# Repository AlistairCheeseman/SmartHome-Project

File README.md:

SmartHome-Project
=================

Final Year degree project to create a set of devices to create a smart home.

Hardware files are created in eagle with PDFs of finished pcbs labelled with which pcb layer they are. Hardware files are created from scratch and a custom library has been created for components not in the default eagle library.

Software has three sections.

	-	www
		copy this to the production web server. the files are based on php 5.6 HTML 5, using ajax and highcharts charting components (http://www.highcharts.com/ - free for non commercial uses).
		
	-	LFS
		This contains a set of manually written build scripts (toolchain and Filesystem) and pre-writted configuration files. After both files (install-*.sh) have been executed on a linux machine there will be a working Linux filesystem. Be sure to change configuration file (buildscript.sh) variables to suit your setup!

	-	Apps
		This contains source for all custom written applications on the server.

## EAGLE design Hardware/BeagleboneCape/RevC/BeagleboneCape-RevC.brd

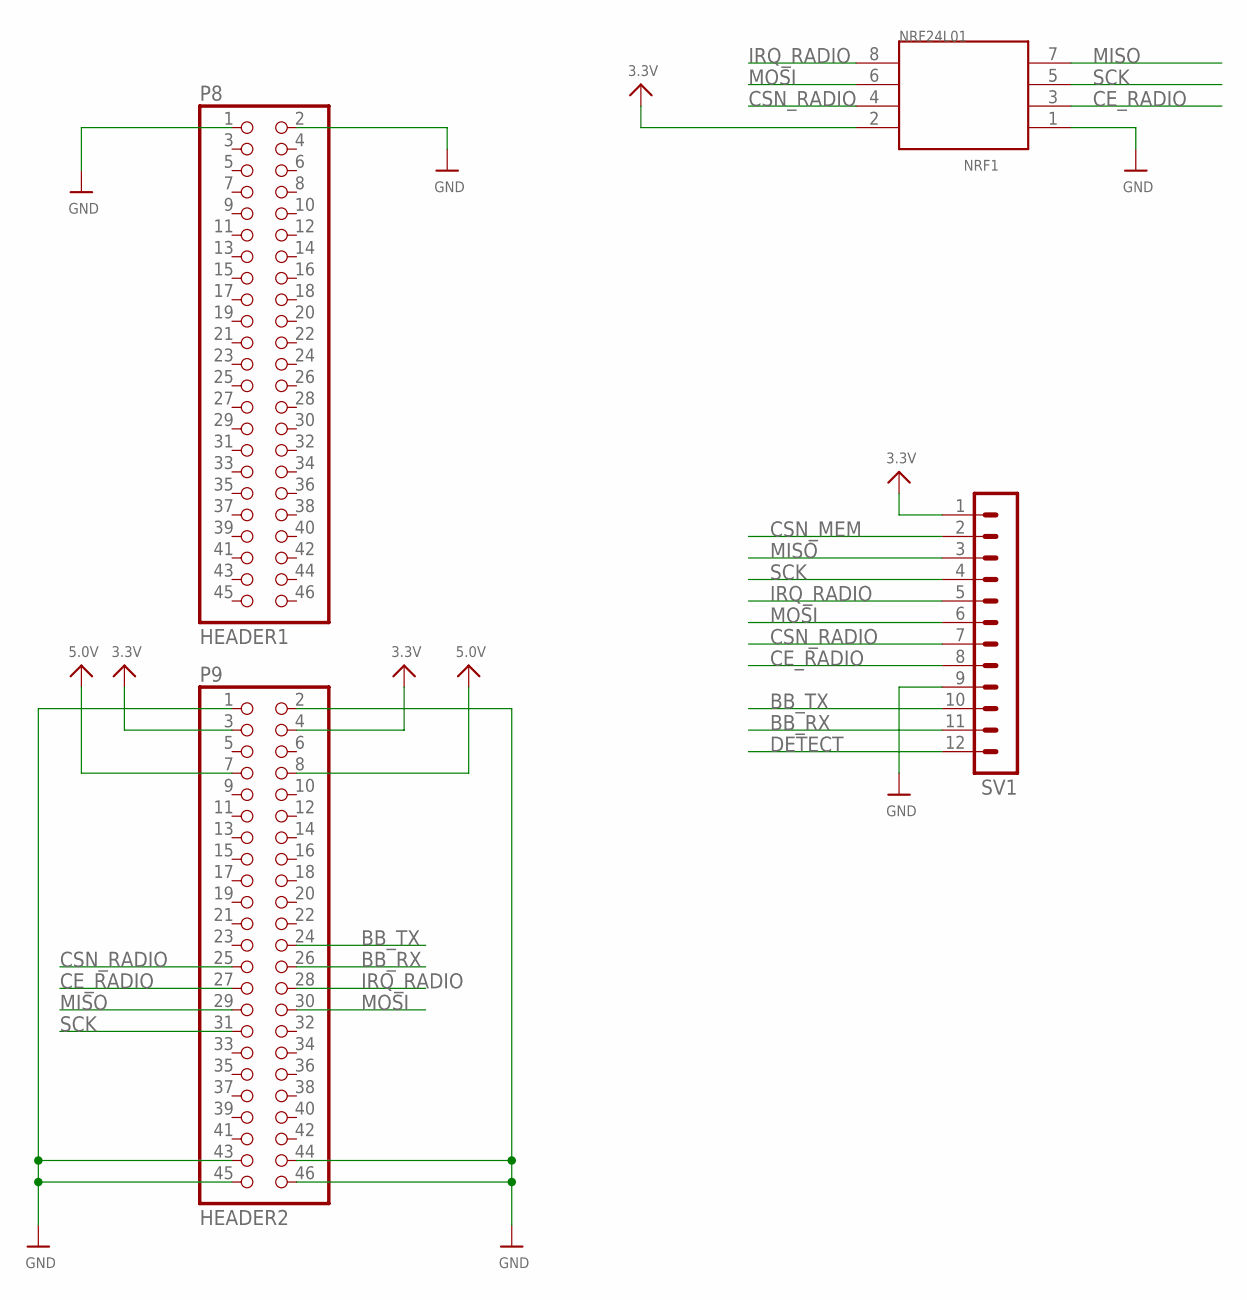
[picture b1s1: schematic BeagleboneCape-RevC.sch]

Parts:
NRF24L01: NRF1; TSM-110-XX-XXX-DV
P8: HEADER1; 2X23
P9: HEADER2; 2X23
SV1: MA12-1

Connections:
3.3V: NRF24L01.2, P9.3, P9.4, SV1.1
5.0V: P9.7, P9.8
BB_RX: P9.26, SV1.11
BB_TX: P9.24, SV1.10
CE_RADIO: NRF24L01.3, P9.27, SV1.8
CSN_MEM: SV1.2
CSN_RADIO: NRF24L01.4, P9.25, SV1.7
DETECT: SV1.12
GND: NRF24L01.1, P8.1, P8.2, P9.1, P9.2, P9.43, P9.44, P9.45, P9.46, SV1.9
IRQ_RADIO: NRF24L01.8, P9.28, SV1.5
MISO: NRF24L01.7, P9.29, SV1.3
MOSI: NRF24L01.6, P9.30, SV1.6
SCK: NRF24L01.5, P9.31, SV1.4

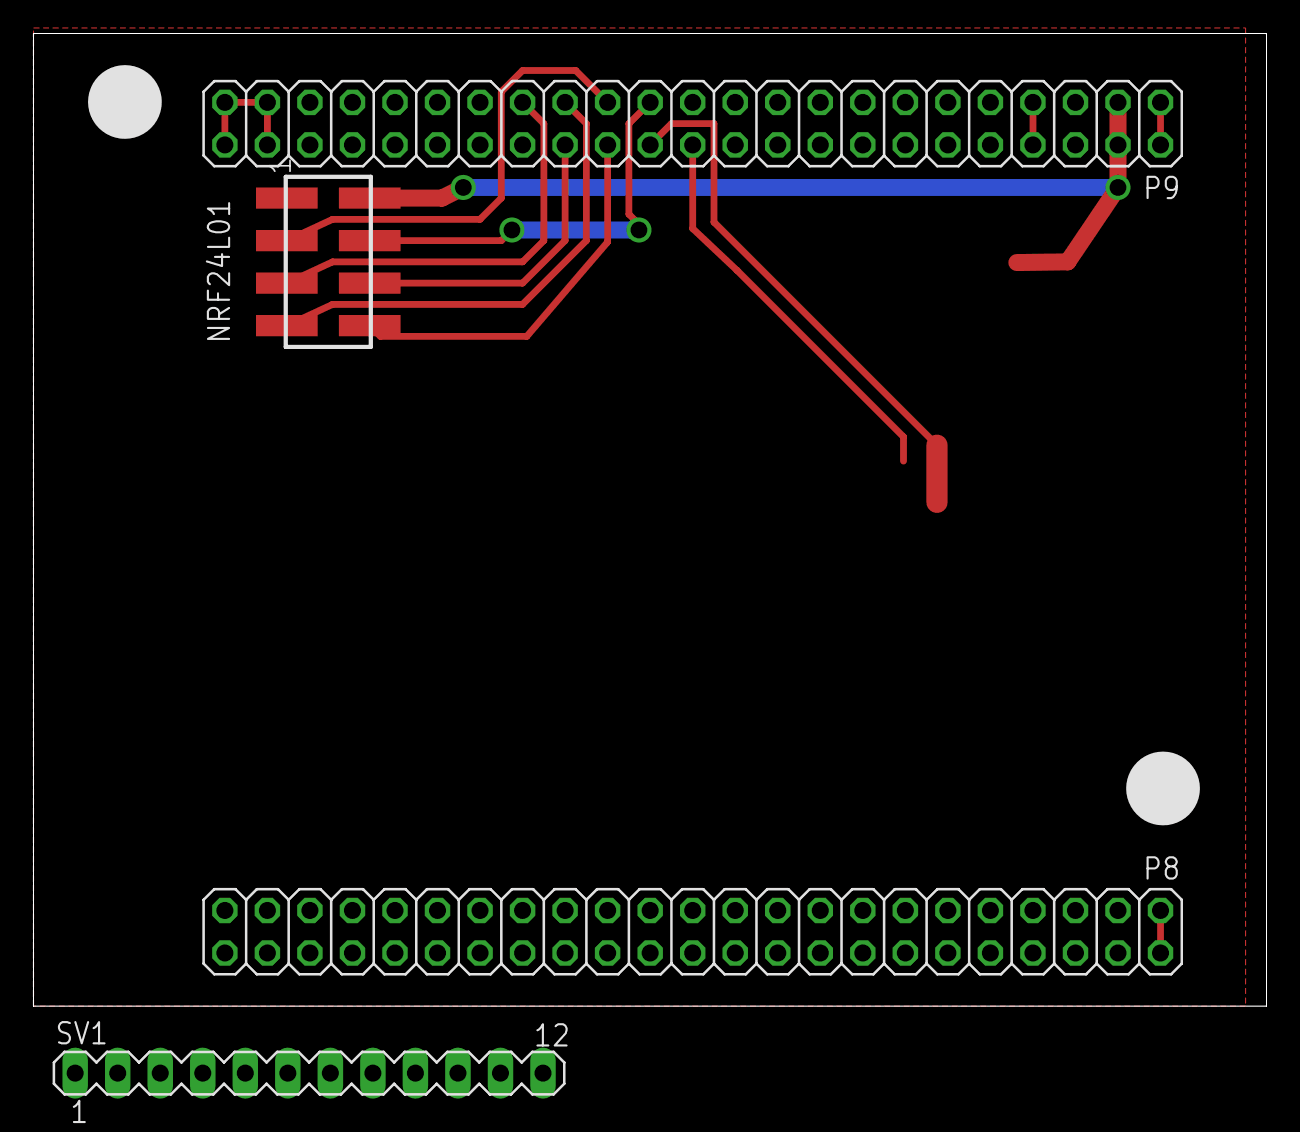
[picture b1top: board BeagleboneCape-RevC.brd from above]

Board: 2 copper layers, 73.6 x 58.1 mm, 4 parts (0 on the bottom side), 11 nets.

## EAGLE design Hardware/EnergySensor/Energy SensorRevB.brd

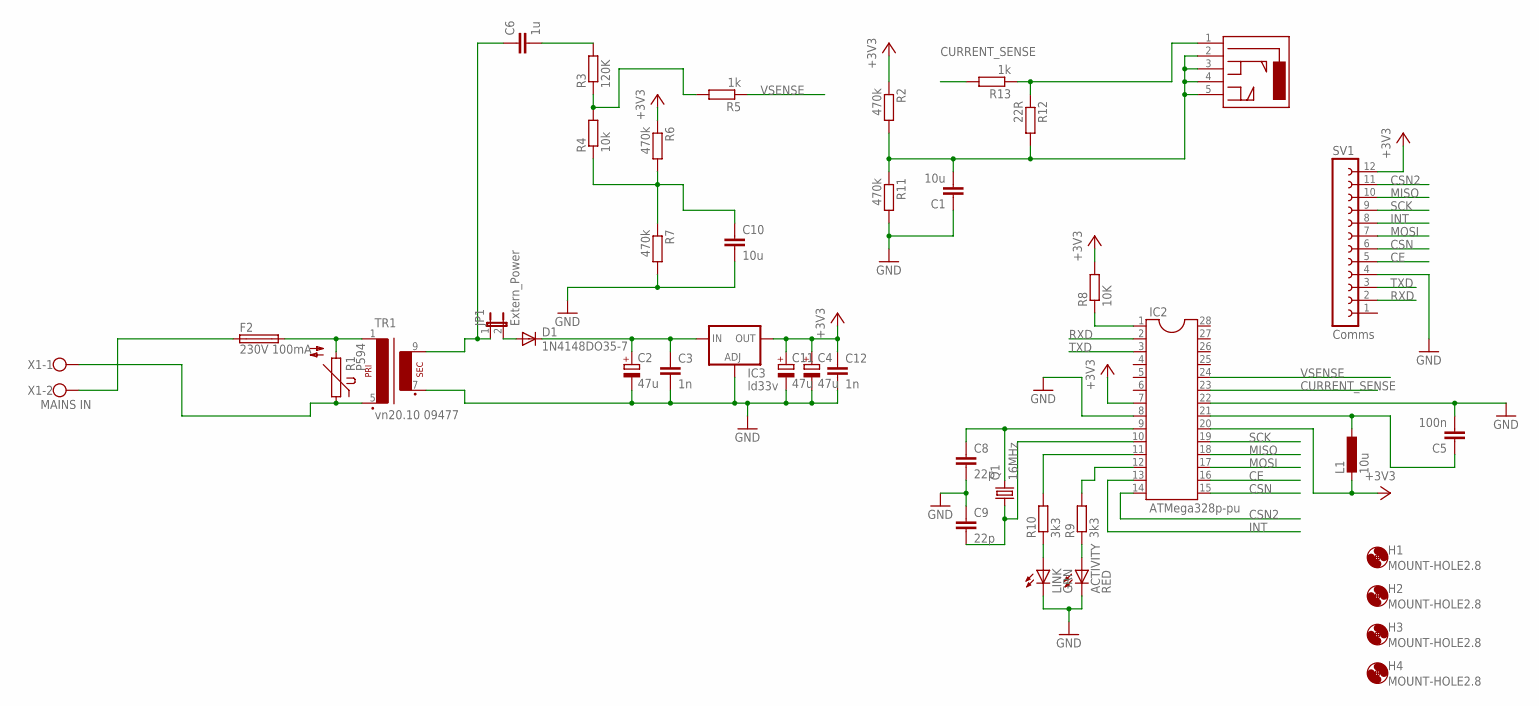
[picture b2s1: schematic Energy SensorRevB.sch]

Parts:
ACTIVITY: RED; LED5MM
C1, C10: 10u; C1206K
C2: 47u; E3,5-10
C3, C12: 1n; C025-025X050
C4, C11: 47u; E3,5-8
C5: 100n; C1206K
C6: 1u; C1206K
C8, C9: 22p; C025-025X050
D1: 1N4148DO35-7; DO35-7
F2: 230V 100mA; SH22,5A
H1, H2, H3, H4: MOUNT-HOLE2.8; 2,8
IC2: ATMega328p-pu; DIL28-3
IC3: ld33v; 317TL
JP1: Extern_Power; JP1
L1: 10u; L3230M
LINK: GRN; LED5MM
Q1: 16MHz; HC49/S
R1: P594
R2, R6, R7, R11: 470k; 0207/7
R3: 120K; 0207/7
R4: 10k; R1206
R5, R13: 1k; 0207/7
R8: 10K; 0207/7
R9, R10: 3k3; 0207/7
R12: 22R; R1206
SV1: Comms; FE12W
TR1: vn20.10 09477; VV11
U$1: 3.5MMJACK
X1: MAINS IN; W237-102

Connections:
+3V3: C4.+, C11.+, C12.1, IC2.7, IC2.20, IC3.2 (OUT), L1.2, R2.1, R6.1, R8.2, SV1.12
CE: IC2.16, SV1.5
CSN: IC2.15, SV1.6
CSN2: IC2.14, SV1.11
CURRENT_SENSE: IC2.23, R13.2
GND: ACTIVITY.K (C), C1.1, C2.-, C3.2, C4.-, C5.2, C8.2, C9.1, C10.2, C11.-, C12.2, IC2.8, IC2.22, IC3.1 (ADJ), LINK.K (C), R7.2, R11.2, SV1.4, TR1.7 (S3)
INT: IC2.13, SV1.8
MISO: IC2.18, SV1.10
MOSI: IC2.17, SV1.7
unnamed: C1.2, R2.2, R11.1, R12.2, U$1.2, U$1.3, U$1.4, U$1.5
unnamed: R1.1, TR1.5 (P2), X1.1
unnamed: D1.A, JP1.2
unnamed: C6.2, R3.2
unnamed: C6.1, JP1.1, TR1.9 (S4)
unnamed: R12.1, R13.1, U$1.1
unnamed: C2.+, C3.1, D1.C, IC3.3 (IN)
unnamed: C5.1, IC2.21, L1.1
unnamed: R3.1, R4.2, R5.2
unnamed: C10.1, R4.1, R6.2, R7.1
unnamed: C8.1, IC2.9, Q1.2
unnamed: C9.2, IC2.10, Q1.1
unnamed: LINK.A, R10.1
unnamed: ACTIVITY.A, R9.1
unnamed: IC2.1, R8.1
unnamed: IC2.12, R9.2
unnamed: IC2.11, R10.2
unnamed: F2.2, R1.2, TR1.1
unnamed: F2.1, X1.2
RXD: IC2.2, SV1.2
SCK: IC2.19, SV1.9
TXD: IC2.3, SV1.3
VSENSE: IC2.24, R5.1

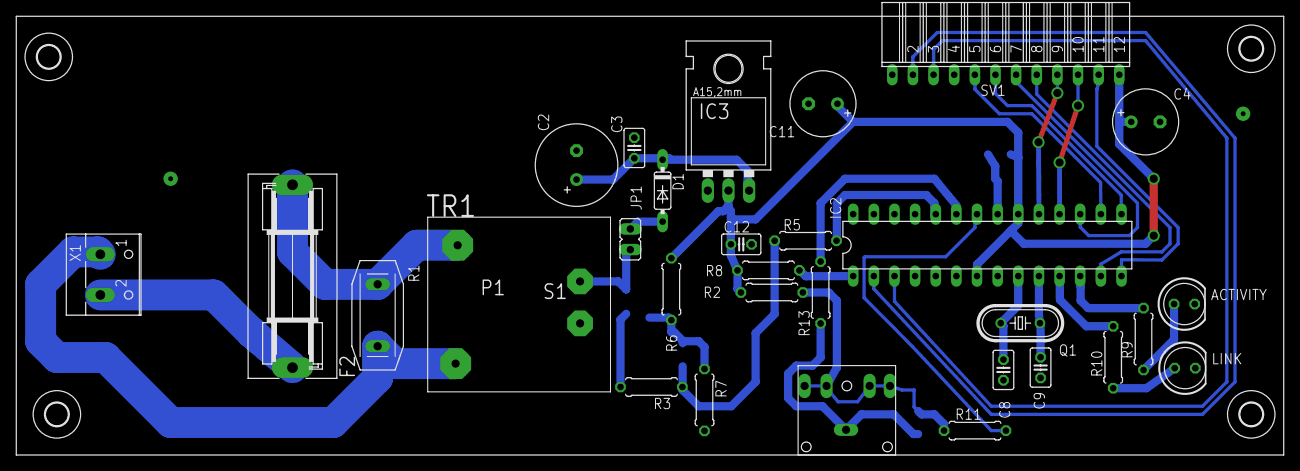
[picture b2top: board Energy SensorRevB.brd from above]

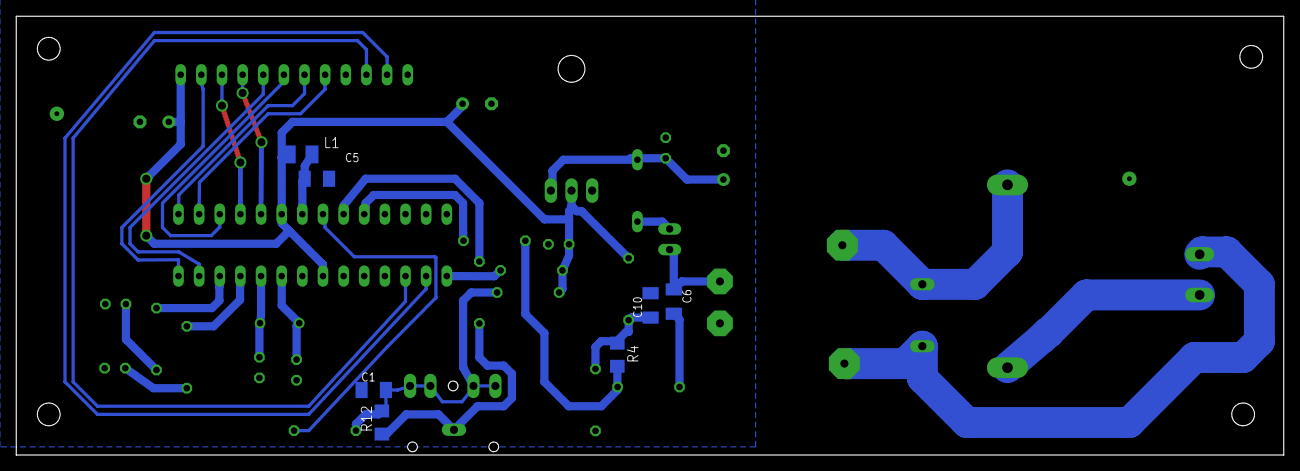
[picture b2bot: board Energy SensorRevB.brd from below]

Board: 2 copper layers, 156.0 x 54.0 mm, 41 parts (7 on the bottom side), 32 nets.

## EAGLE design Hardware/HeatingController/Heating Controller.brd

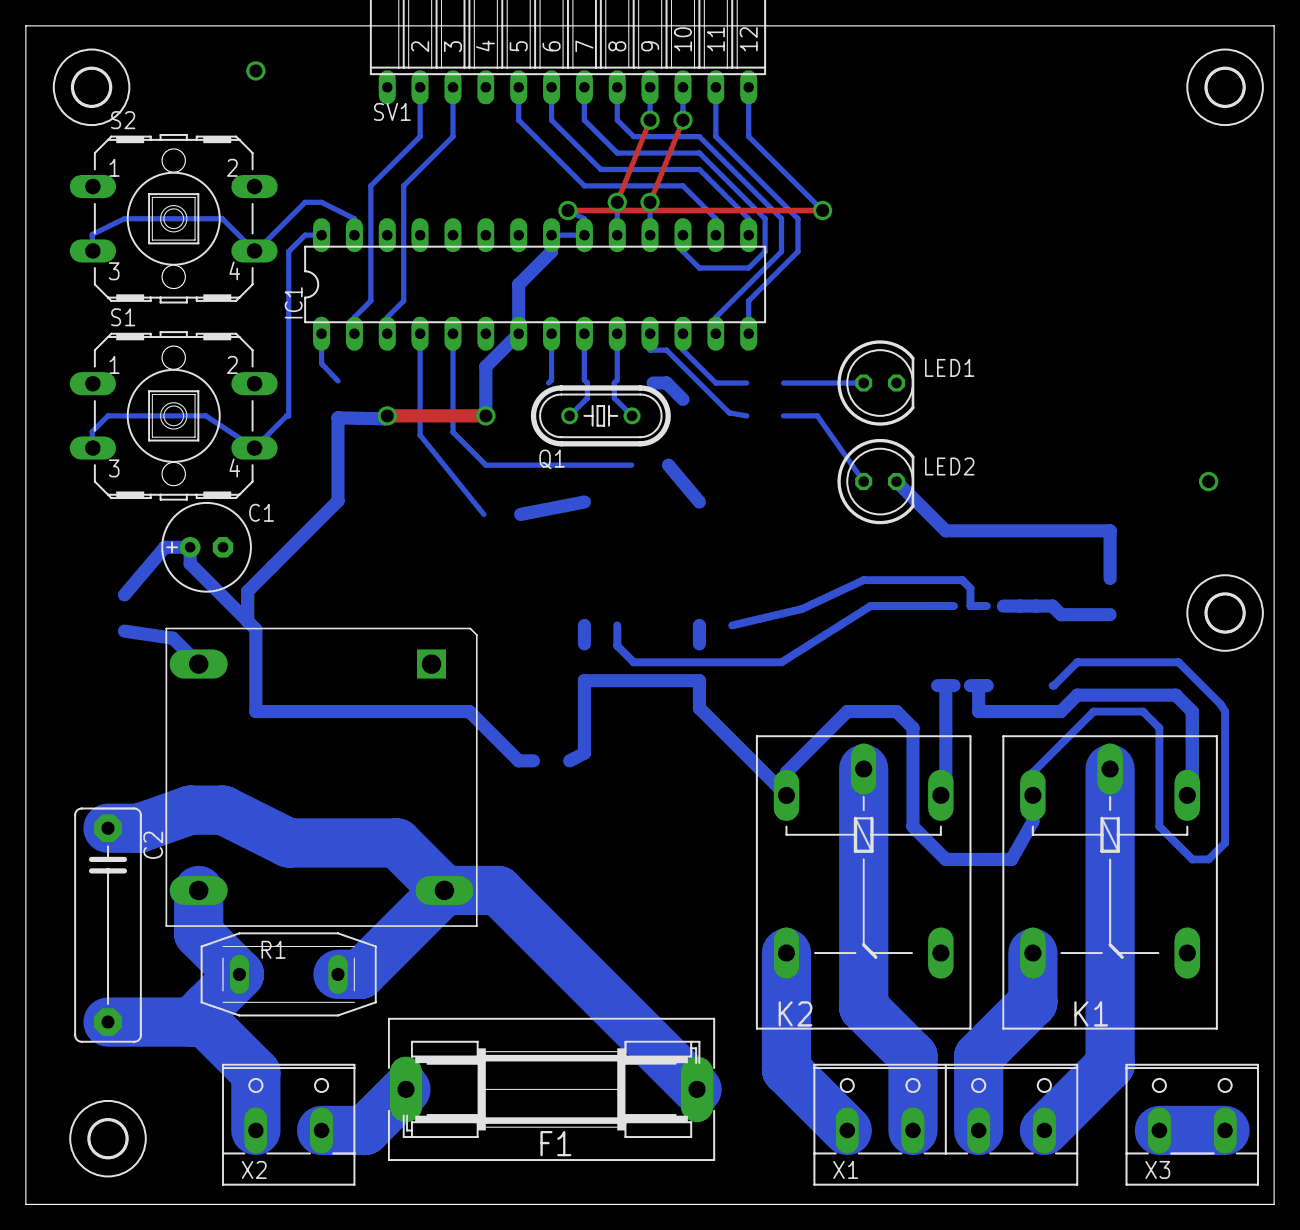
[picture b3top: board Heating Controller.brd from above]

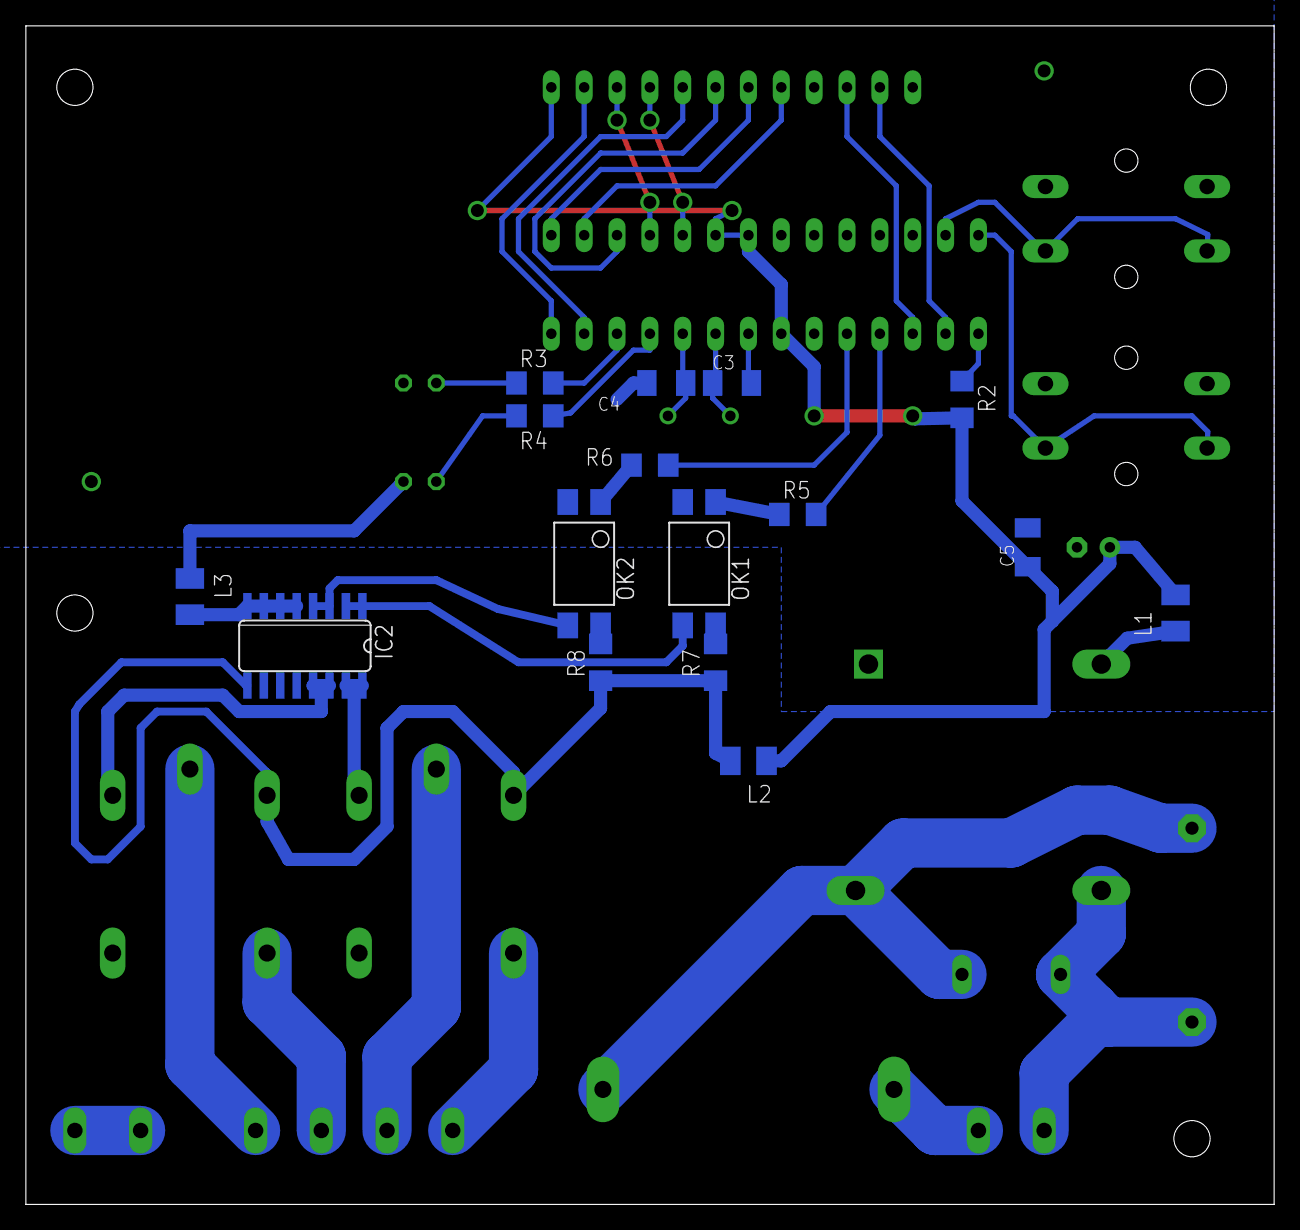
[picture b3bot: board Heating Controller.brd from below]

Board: 2 copper layers, 96.5 x 91.1 mm, 37 parts (16 on the bottom side), 41 nets.

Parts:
C1: 47u; E2,5-7
C2: 0.1u/275V; C15B5
C3, C4: 22p; C1206K
C5: 0.1u; C1206K
F1: 230V 70mA; SH22,5A
H1, H2, H3, H4: MOUNT-HOLE2.8; 2,8
IC1: ATMega 328p-pu; DIL28-3
IC2: ULN2003AD; SO16
K1, K2: G5LE
L1, L2, L3: L3230M
LED1: HEAT; LED5MM
LED2: WATER; LED5MM
OK1, OK2: LTV816S; DIL4-SMD
Q1: 16MHz; HC49/S
R1: P594
R2: 10k; R1206
R3, R4: 3k3; R1206
R5, R6, R7, R8: 120R; R1206
S1: WATER_BOOST; B3F-40XX
S2: HEATING_BOOST; B3F-40XX
SV1: Comms; FE12W
U$1: VTX-214-001-103; VTX214001103
X1: SWITCHED_OUT; W237-4P
X2: MAINS IN; W237-132
X3: NEUTRAL; W237-132

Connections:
+3V3: C1.+, C5.1, IC1.7, IC1.20, IC1.21, L1.2, L2.1, R2.2, SV1.12
+3V3A: L1.1, U$1.2
AGND: IC2.5, IC2.6, IC2.7, IC2.8, L3.2
CE: IC1.16, SV1.5
CSN: IC1.15, SV1.6
CSN2: IC1.14, SV1.11
GND: C1.-, C3.2, C4.2, C5.2, IC1.8, IC1.22, L3.1, LED1.K, LED2.K, OK1.2, OK2.2, S1.1, S1.2, S2.1, S2.2, SV1.4, U$1.1
HEATING_R: IC1.5, R6.2
HEATL: IC1.11, R4.2
HOTWATERL: IC1.12, R3.2
HOTWATER_R: IC1.4, R5.2
INT: IC1.13, SV1.8
MISO: IC1.18, SV1.10
MOSI: IC1.17, SV1.7
unnamed: F1.1, X2.2
unnamed: C2.1, F1.2, R1.2, U$1.4
unnamed: C2.2, R1.1, U$1.3, X2.1
unnamed: IC1.1, R2.1
unnamed: C3.1, IC1.9, Q1.2
unnamed: C4.1, IC1.10, Q1.1
unnamed: LED1.A, R3.1
unnamed: LED2.A, R4.1
unnamed: IC1.28, S1.3, S1.4
unnamed: IC1.27, S2.3, S2.4
unnamed: OK1.1, R5.1
unnamed: IC2.15, IC2.16, K2.2
unnamed: IC2.13, IC2.14, K1.2
unnamed: OK2.1, R6.1
unnamed: K2.P, X1.2
unnamed: K2.S, X1.1
unnamed: K1.P, X1.4
unnamed: K1.S, X1.3
unnamed: X3.1, X3.2
unnamed: OK1.4, R7.2
unnamed: OK2.4, R8.2
unnamed: IC2.1, IC2.2, OK1.3
unnamed: IC2.3, IC2.4, OK2.3
RXD: IC1.2, SV1.2
SCK: IC1.19, SV1.9
TXD: IC1.3, SV1.3
VCC: IC2.9, K1.1, K2.1, L2.2, R7.1, R8.1

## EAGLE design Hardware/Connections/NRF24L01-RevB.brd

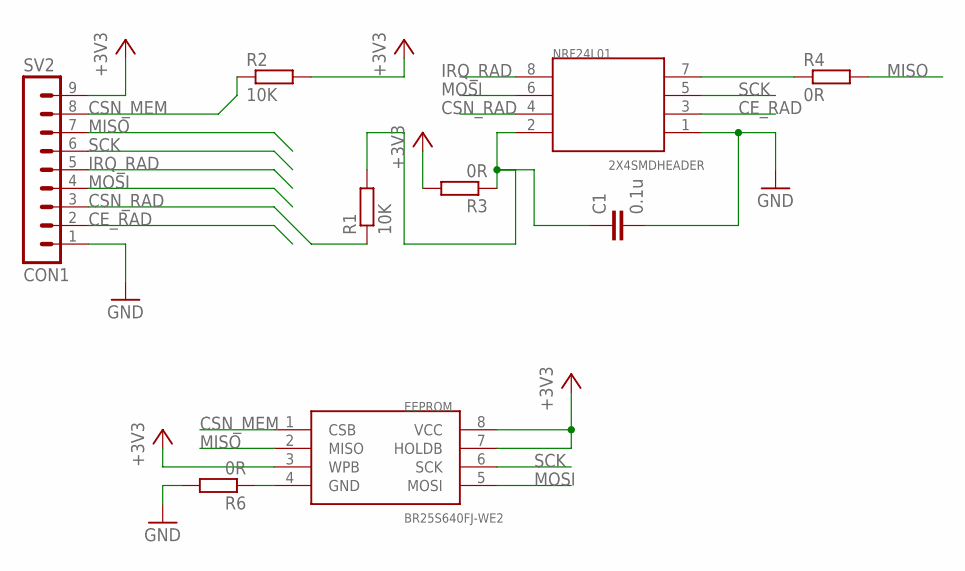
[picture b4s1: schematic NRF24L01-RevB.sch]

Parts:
C1: 0.1u; C1206K
EEPROM: BR25S640FJ-WE2; SO8
NRF24L01: 2X4SMDHEADER; TSM-110-XX-XXX-DV
R1, R2: 10K; R1206
R3, R4, R6: 0R; R1206
SV2: CON1; MA09-1W

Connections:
+3V3: EEPROM.3 (WPB), EEPROM.7 (HOLDB), EEPROM.8 (VCC), R2.2, R3.2, SV2.9
CE_RAD: NRF24L01.3, SV2.2
CSN_MEM: EEPROM.1 (CSB), R2.1, SV2.8
CSN_RAD: NRF24L01.4, R1.1, SV2.3
GND: C1.2, NRF24L01.1, R6.2, SV2.1
IRQ_RAD: NRF24L01.8, SV2.5
MISO: EEPROM.2 (MISO), R4.2, SV2.7
MOSI: EEPROM.5 (MOSI), NRF24L01.6, SV2.4
unnamed: C1.1, NRF24L01.2, R1.2, R3.1
unnamed: NRF24L01.7, R4.1
unnamed: EEPROM.4 (GND), R6.1
SCK: EEPROM.6 (SCK), NRF24L01.5, SV2.6

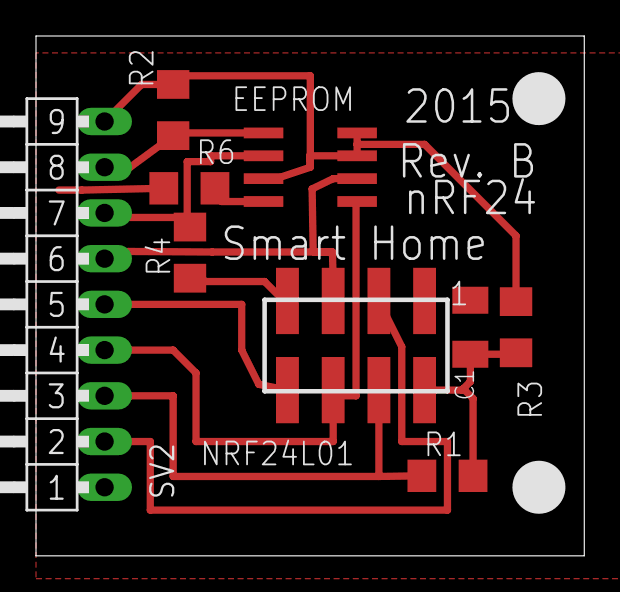
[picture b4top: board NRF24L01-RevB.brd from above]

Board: 2 copper layers, 30.5 x 28.9 mm, 9 parts (0 on the bottom side), 12 nets.

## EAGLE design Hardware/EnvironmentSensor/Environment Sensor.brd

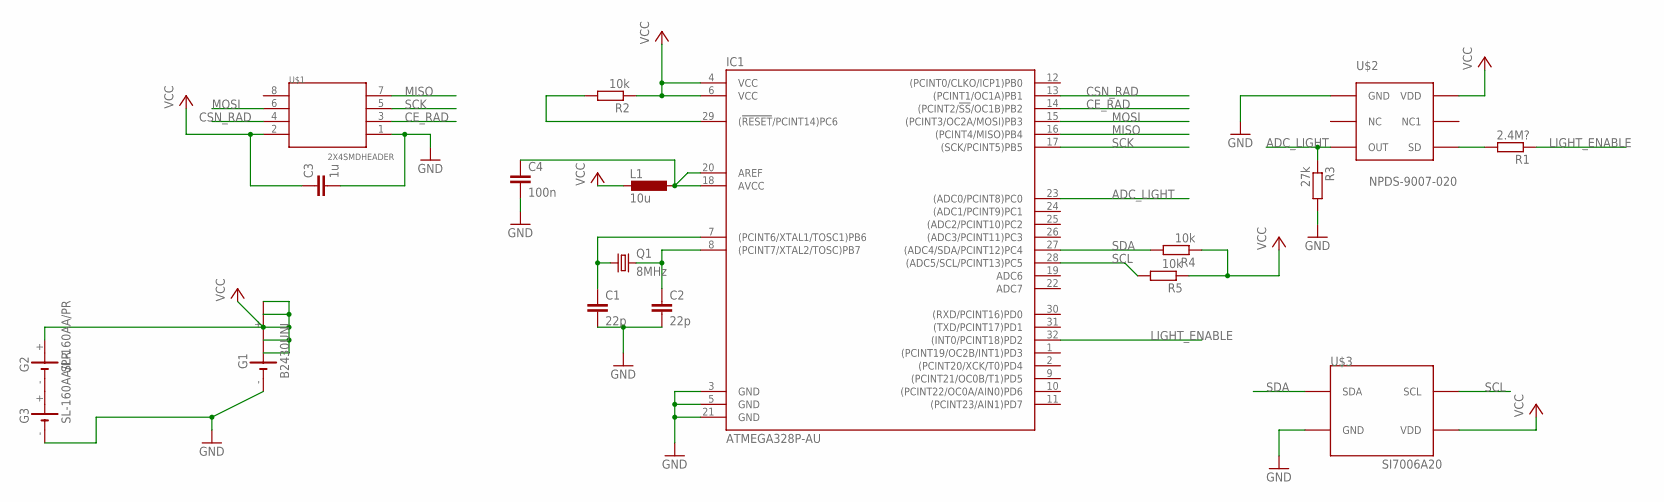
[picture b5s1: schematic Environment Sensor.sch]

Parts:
C1, C2: 22p; C1206K
C3: 1u; C1206K
C4: 100n; C1206
G1: B2430UNI
G2, G3: SL-160AA/PR
IC1: ATMEGA328P-AU; TQFP32-08
L1: 10u; L3216C
Q1: 8MHz; HC49UP
R1: 2.4M?; R1206
R2, R4, R5: 10k; R1206
R3: 27k; R1206
U$1: 2X4SMDHEADER; TSM-110-XX-XXX-DV
U$2: NPDS-9007-020; APDS-9007
U$3: SI7006A20; 3X3DFN

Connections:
ADC_LIGHT: IC1.23 ((ADC0/PCINT8)PC0), R3.1, U$2.P$3 (OUT)
CE_RAD: IC1.14 ((PCINT2/!SS!/OC1B)PB2), U$1.3
CSN_RAD: IC1.13 ((PCINT1/OC1A)PB1), U$1.4
GND: C1.2, C2.2, C3.2, C4.2, G1.-, G3.-, IC1.3 (GND), IC1.5 (GND), IC1.21 (GND), R3.2, U$1.1, U$2.P$1 (GND), U$3.P$2 (GND)
LIGHT_ENABLE: IC1.32 ((INT0/PCINT18)PD2), R1.1
MISO: IC1.16 ((PCINT4/MISO)PB4), U$1.7
MOSI: IC1.15 ((PCINT3/OC2A/MOSI)PB3), U$1.6
unnamed: C1.1, IC1.7 ((PCINT6/XTAL1/TOSC1)PB6), Q1.1
unnamed: C2.1, IC1.8 ((PCINT7/XTAL2/TOSC)PB7), Q1.2
unnamed: IC1.29 ((!RESET!/PCINT14)PC6), R2.2
unnamed: G2.-, G3.+
unnamed: R1.2, U$2.P$6 (SD)
unnamed: C4.1, IC1.18 (AVCC), IC1.20 (AREF), L1.1
SCK: IC1.17 ((SCK/PCINT5)PB5), U$1.5
SCL: IC1.28 ((ADC5/SCL/PCINT13)PC5), R5.2, U$3.P$6 (SCL)
SDA: IC1.27 ((ADC4/SDA/PCINT12)PC4), R4.2, U$3.P$1 (SDA)
VCC: C3.1, G1.+, G1.+@1 (+), G1.+@2 (+), G1.+@3 (+), G1.+@4 (+), G2.+, IC1.4 (VCC), IC1.6 (VCC), L1.2, R2.1, R4.1, R5.1, U$1.2, U$2.P$4 (VDD), U$3.P$5 (VDD)

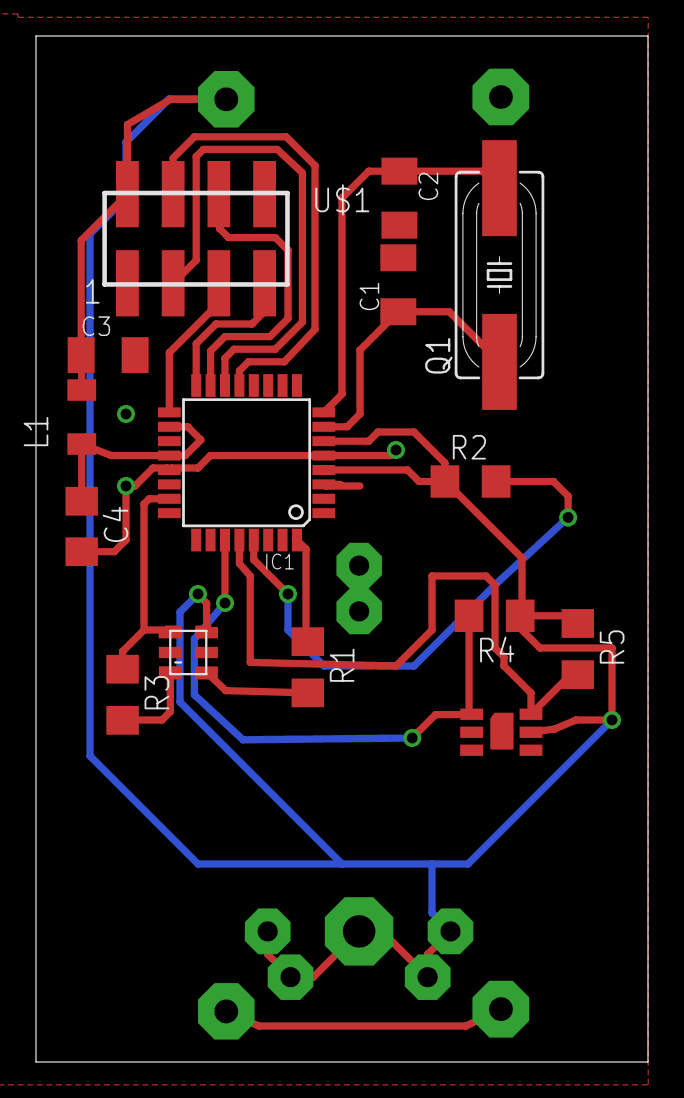
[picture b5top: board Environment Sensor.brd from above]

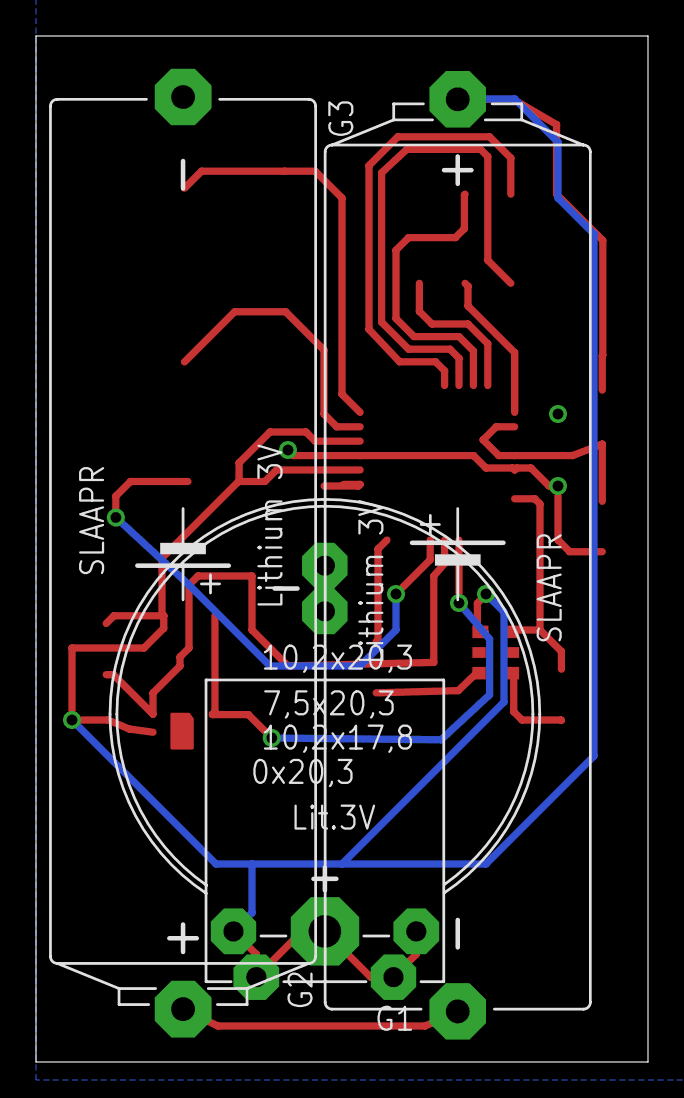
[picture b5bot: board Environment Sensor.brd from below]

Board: 2 copper layers, 34.0 x 57.0 mm, 18 parts (3 on the bottom side), 17 nets.

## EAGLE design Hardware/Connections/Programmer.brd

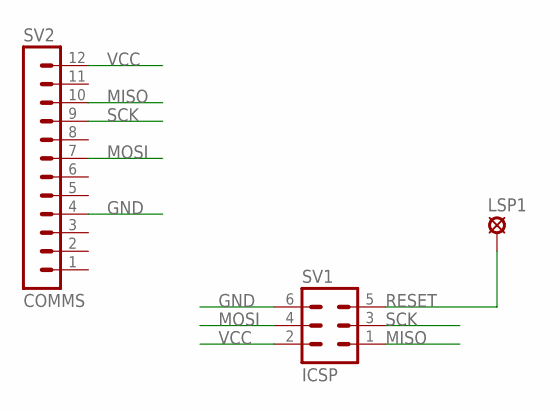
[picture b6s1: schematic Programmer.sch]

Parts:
LSP1: MCS10B
SV1: ICSP; MA03-2
SV2: COMMS; MA12-1W

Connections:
GND: SV1.6, SV2.4
MISO: SV1.1, SV2.10
MOSI: SV1.4, SV2.7
RESET: LSP1.MP, SV1.5
SCK: SV1.3, SV2.9
VCC: SV1.2, SV2.12

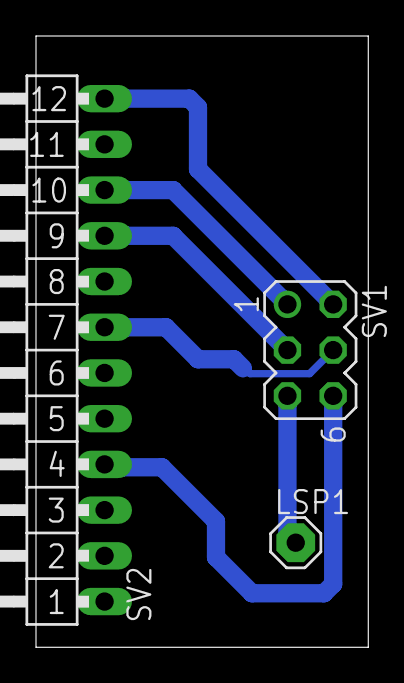
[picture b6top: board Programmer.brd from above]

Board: 2 copper layers, 18.5 x 34.0 mm, 3 parts (0 on the bottom side), 6 nets.

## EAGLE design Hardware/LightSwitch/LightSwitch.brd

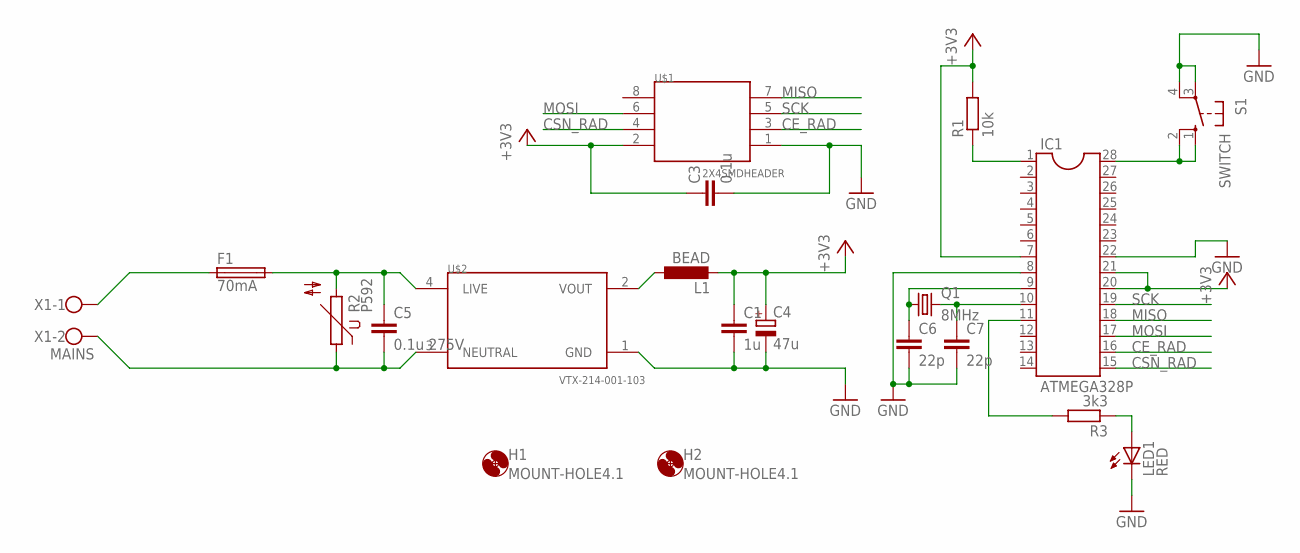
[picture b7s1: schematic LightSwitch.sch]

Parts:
C1: 1u; C1206K
C3: 0.1u; C1206
C4: 47u; E2,5-6E
C5: 0.1u 275V; C15B5
C6, C7: 22p; C1206
F1: 70mA; SH22,5A
H1, H2: MOUNT-HOLE4.1; 4,1
IC1: ATMEGA328P; DIL28-3
L1: BEAD; L3230M
LED1: RED; LED5MM
Q1: 8MHz; HC49U70
R1: 10k; R1206
R2: P592
R3: 3k3; R1206
S1: SWITCH; B3F-40XX
U$1: 2X4SMDHEADER; TSM-110-XX-XXX-DV
U$2: VTX-214-001-103; VTX214001103
X1: MAINS; W237-102

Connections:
+3V3: C1.1, C3.1, C4.+, IC1.7, IC1.20, IC1.21, L1.2, R1.2, U$1.2
CE_RAD: IC1.16, U$1.3
CSN_RAD: IC1.15, U$1.4
GND: C1.2, C3.2, C4.-, C6.2, C7.2, IC1.8, IC1.22, LED1.K (C), S1.3, S1.4 (P1), U$1.1, U$2.1 (GND)
MISO: IC1.18, U$1.7
MOSI: IC1.17, U$1.6
unnamed: F1.1, X1.1
unnamed: C5.1, F1.2, R2.2, U$2.4 (LIVE)
unnamed: IC1.1, R1.1
unnamed: C5.2, R2.1, U$2.3 (NEUTRAL), X1.2
unnamed: IC1.11, R3.2
unnamed: LED1.A, R3.1
unnamed: IC1.28, S1.1 (S), S1.2 (S1)
unnamed: C6.1, IC1.9, Q1.1
unnamed: C7.1, IC1.10, Q1.2
SCK: IC1.19, U$1.5
VOUT: L1.1, U$2.2 (VOUT)

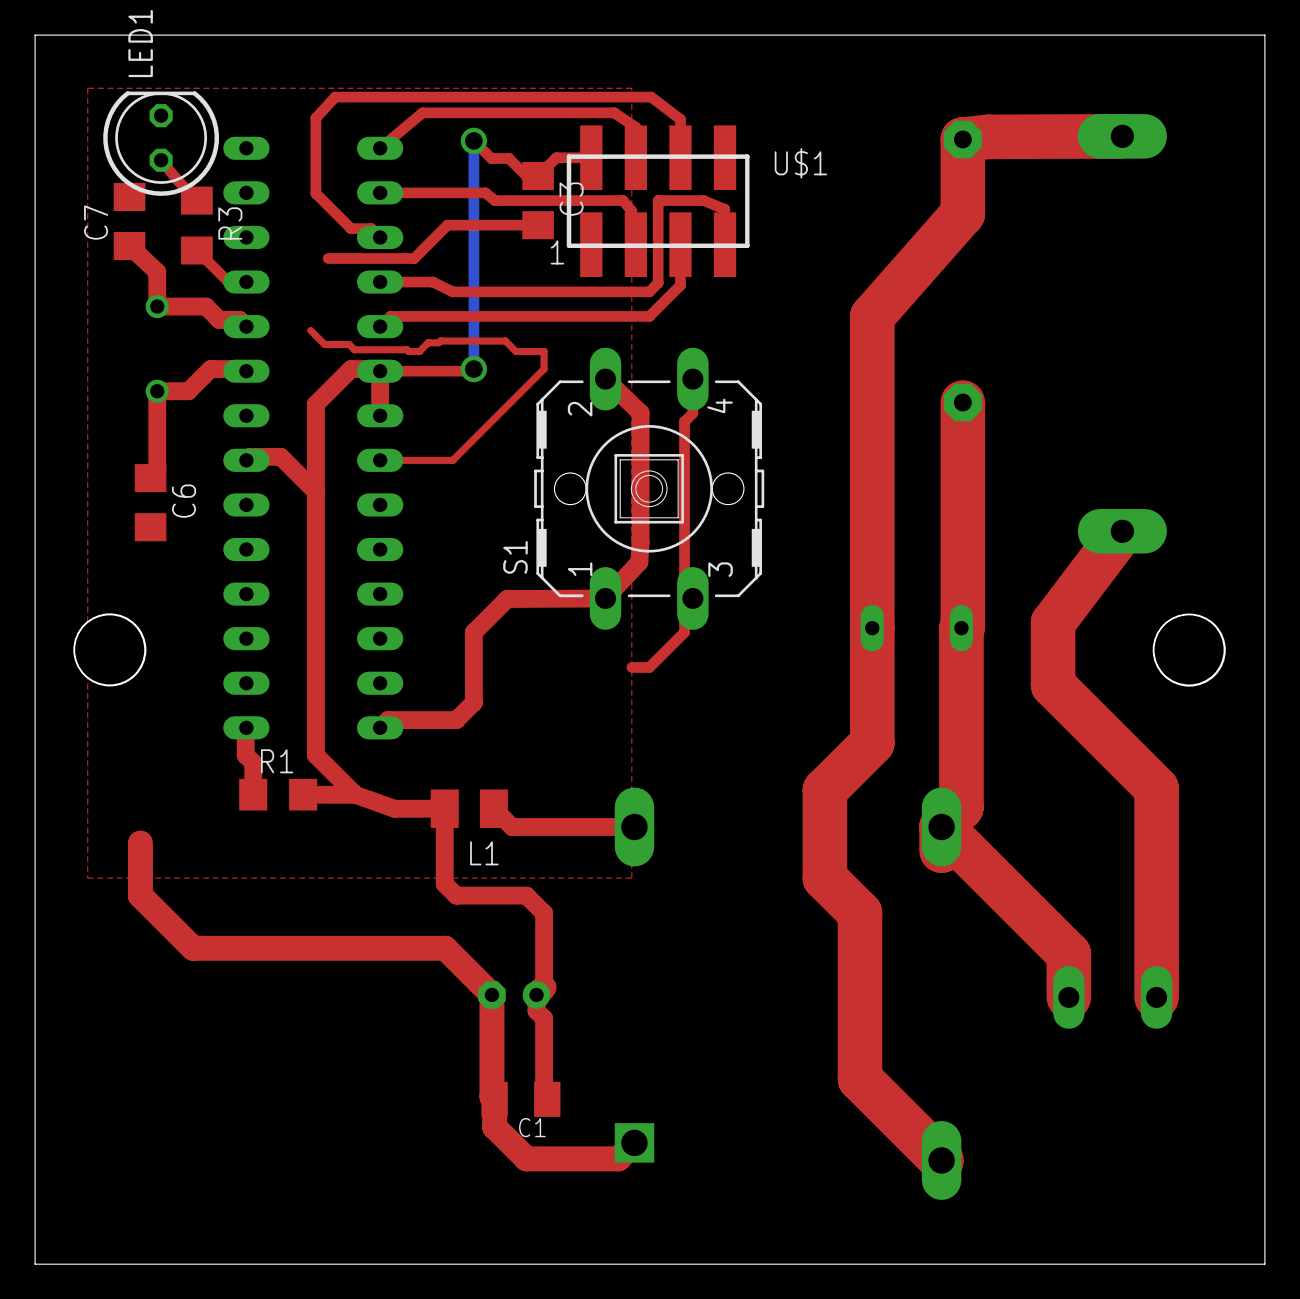
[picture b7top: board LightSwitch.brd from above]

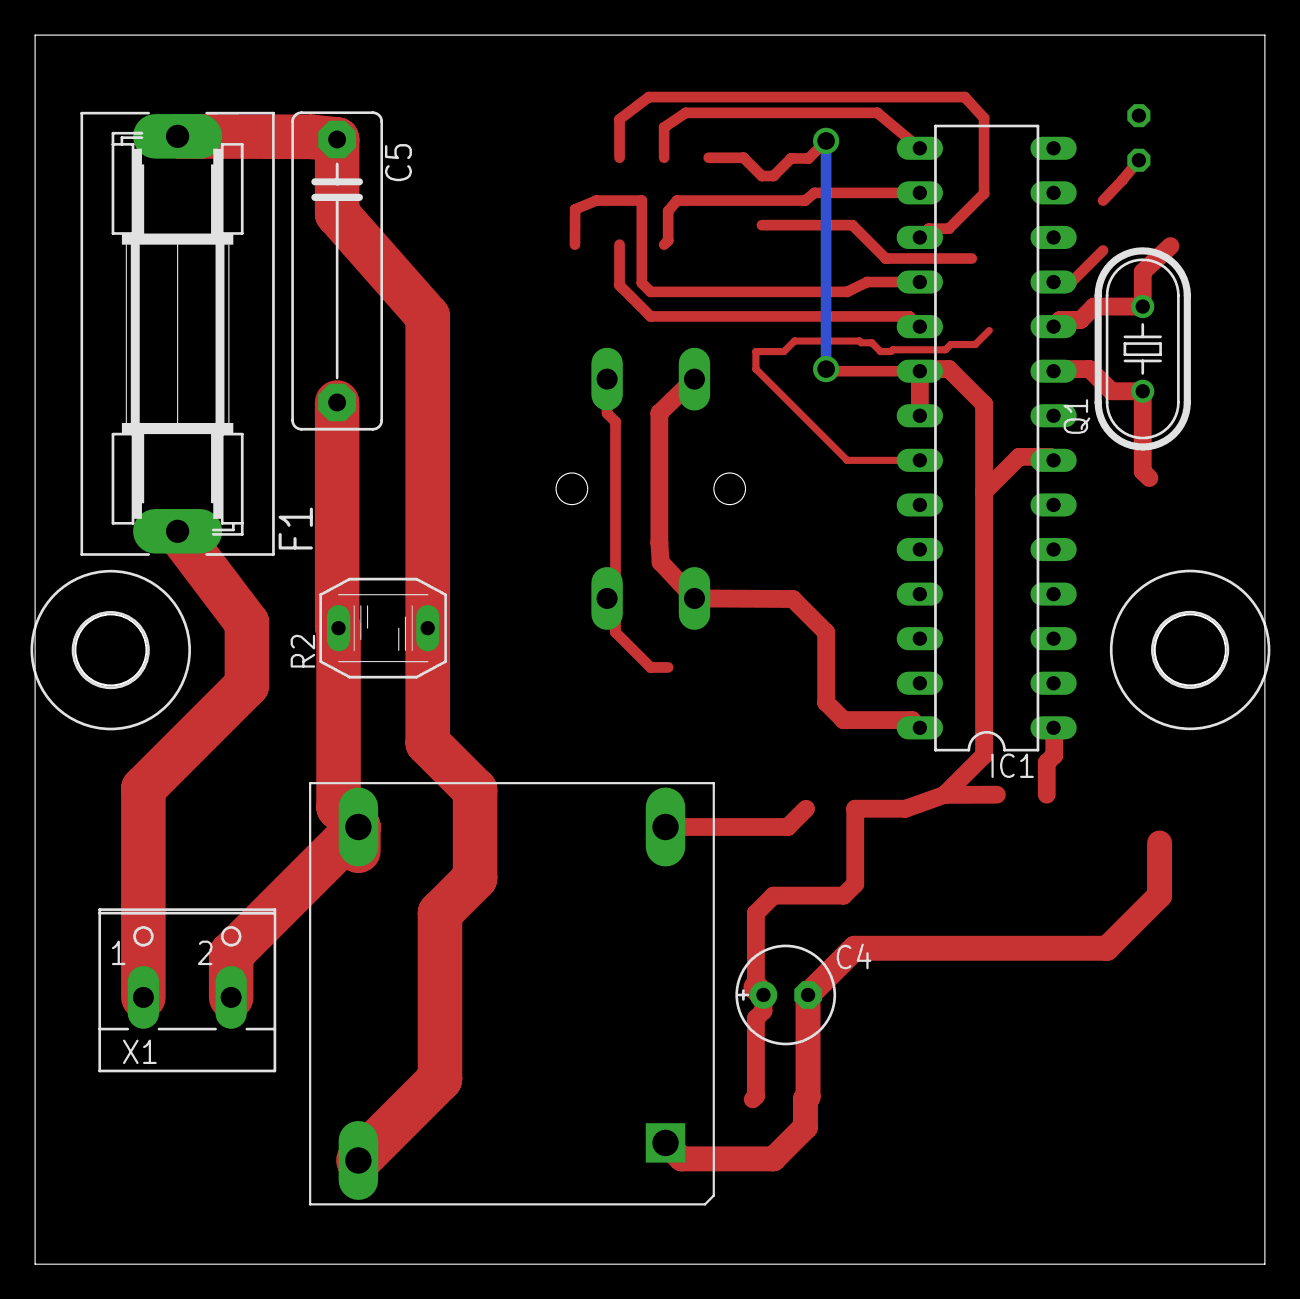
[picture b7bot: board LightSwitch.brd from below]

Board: 2 copper layers, 70.1 x 70.0 mm, 20 parts (10 on the bottom side), 17 nets.
